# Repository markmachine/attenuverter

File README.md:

# Repository Title Goes Here

> Subtitle or Short Description Goes Here

> ideally one sentence

> include terms/tags that can be searched

**Badges will go here**

- build status
- issues (waffle.io maybe)
- devDependencies
- npm package
- coverage
- slack
- downloads
- gitter chat
- license
- etc.

## KiCad Euroarack Resources

http://smisioto.no-ip.org/elettronica/kicad/kicad-en.htm

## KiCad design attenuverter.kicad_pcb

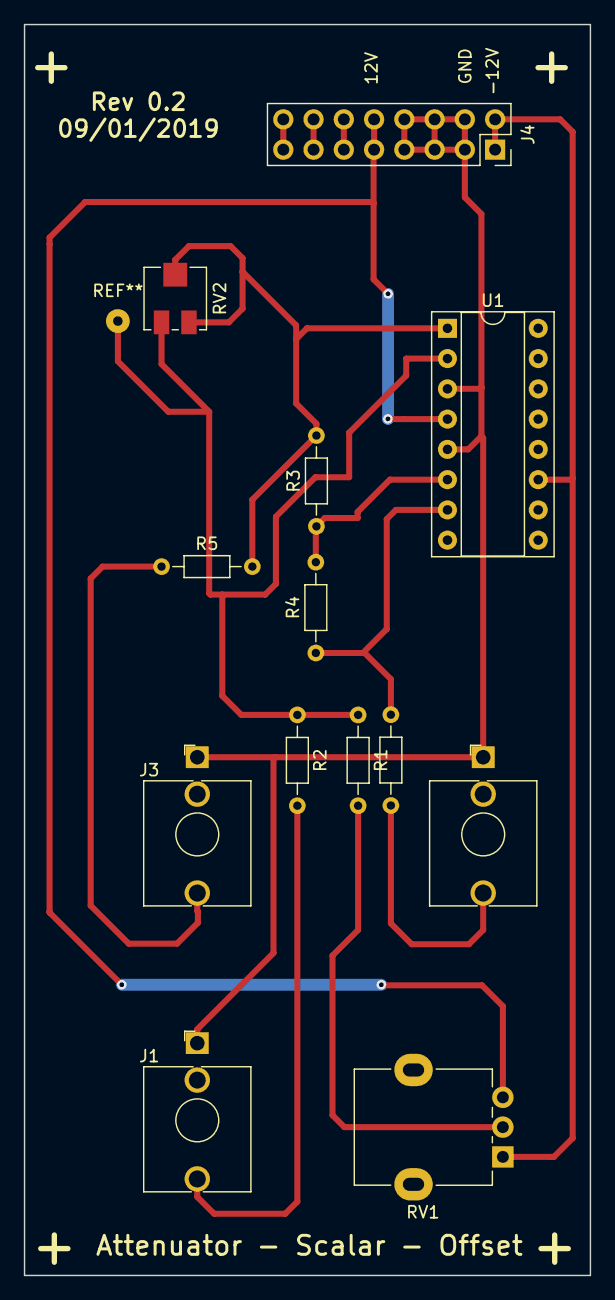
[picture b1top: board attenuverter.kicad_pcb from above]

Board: 2 copper layers, 47.5 x 105.0 mm, 13 parts (0 on the bottom side), 14 nets.

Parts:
J1: Input; Jack_3.5mm_QingPu_WQP-PJ398SM_Vertical_CircularHoles
J2: Output; Jack_3.5mm_QingPu_WQP-PJ398SM_Vertical_CircularHoles
J3: Inverted Out; Jack_3.5mm_QingPu_WQP-PJ398SM_Vertical_CircularHoles
J4: HEADER_8x2; PinSocket_2x08_P2.54mm_Vertical
R1, R2, R3, R4: 10K; R_Axial_DIN0204_L3.6mm_D1.6mm_P7.62mm_Horizontal
R5, R6: 1K; R_Axial_DIN0204_L3.6mm_D1.6mm_P7.62mm_Horizontal
RV1: 10K; Potentiometer_Alpha_RD901F-40-00D_Single_Vertical
RV2: 100K; Potentiometer_Vishay_TS53YJ_Vertical
U1: TL074; DIP-16_W7.62mm_Socket

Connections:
+12V: J4.9, J4.10, RV1.3, U1.4
-12V: J4.1, J4.2, RV1.1, U1.11
GND: J1.S, J2.S, J3.S, J4.3, J4.4, J4.5, J4.6, J4.7, J4.8, U1.3, U1.5
unnamed: J1.T, R2.2
unnamed: J2.T, R6.1
unnamed: J3.T, R5.1
unnamed: J4.11, J4.12
unnamed: J4.13, J4.14
unnamed: J4.15, J4.16
unnamed: R1.1, R2.1, RV2.3, U1.2
unnamed: R1.2, RV1.2
unnamed: R3.1, R4.2, U1.6
unnamed: R3.2, R5.2, RV2.1, RV2.2, U1.1
unnamed: R4.1, R6.2, U1.7

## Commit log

2019-09-11 add readme
2019-09-11 moving current KiCad files
2019-09-11 resources
